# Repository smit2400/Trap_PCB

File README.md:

# TRAP — Solar-Powered Pest Trap Controller

A solar battery charger and LED driver for agricultural pest traps, built around a **Renesas RL78/G12** microcontroller with **bare-metal C** firmware. Developed at Shriji Technoaspire in 2022. By day the board charges a Li-ion battery pack from a solar panel; at night it runs from the battery and drives four LED towers that attract insects and light the farm.

*Main board, rev 2.0 — 2-layer, 61 × 70 mm (rendered from the KiCad layout)*

---

## Overview

Small farms need insect control that runs unattended and off-grid. TRAP is a single board that handles the whole day/night cycle on its own:

- **Day:** detects solar input, charges the battery and stops charging when the battery is full.
- **Night:** detects that the solar voltage has dropped and powers the LED towers from the battery.
- **Protection:** cuts the load when the battery runs low and stays off until the sun returns, so the pack is never deep-discharged.

I designed the schematic and PCB in KiCad, wrote the firmware in C, and built an Arduino-based serial programmer to flash the RL78 boards.

## Key specs

| | |
|---|---|
| **MCU** | Renesas RL78/G12 (R5F102AA), 30-pin SSOP |
| **Firmware** | Bare-metal Embedded C, Renesas CS+ / CA78K0R, Code Generator drivers |
| **Power in** | Solar panel |
| **Storage** | Li-ion battery pack, low-battery cutoff at ~7.0 V |
| **Load** | 4 LED towers via JST-EH connectors |
| **Logic supply** | MC78L05 5 V regulator |
| **Main PCB** | 2 layers, 61 × 70 mm, KiCad 6 |
| **Indicators** | CHARGING and LOW BAT status LEDs |

## Hardware

```
Solar panel ──► Schottky / Zener protection ──► Charge switch ──► Li-ion pack
                                                                     │
                     RL78 MCU ◄── ADC: solar & battery dividers ◄────┤
                        │                                            │
                        ├── charge enable / indicator LEDs           ▼
                        └── pulse output ──► LED driver (boost) ──► 4 × LED towers
```

**Main board** (`hardware/main-board/`)
- No KiCad footprint was available for the RL78/G12, so the 30-pin RL78/G13 (R5F100AC) symbol and footprint were used. This is why the schematic and BOM list the G13 part.
- Solar and battery voltages are scaled through resistor dividers into two RL78 ADC channels.
- Charging path uses SS24 Schottky diodes for reverse-current blocking and Zener clamping, with SOT-23 transistors and MOSFETs (AO3400A, TP0610T, BC847) switching the charge and load paths.
- An MC78L05 provides the 5 V logic rail.
- A 4-pin header exposes the programming and debug lines for in-circuit flashing.
- Power traces were widened from a 1.0 mm maximum in rev 1.0 to up to 1.5 mm in rev 2.0, and the ground track was widened for current handling.

**LED tower board** (`hardware/led-board/`)
- A narrow 100 × 14 mm strip of SMD LEDs; four of these form the light towers.

## Firmware

Written in bare-metal C on top of the Renesas Code Generator peripheral drivers (`r_cg_*`). The application logic lives in `r_main.c` and `r_cg_timer_user.c`.

**Sampling (timer interrupt).** Timer TAU0 channel 0 fires periodically. Each interrupt alternates between the solar ADC channel (16) and the battery ADC channel (17), accumulating samples into a moving average: 5 samples for solar, 20 for battery. The longer battery average filters out dips caused by the pulsed LED load.

**Control (main loop state machine).**

| State | Condition | Action |
|---|---|---|
| **Night / LEDs on** | Solar low, battery OK | Pulse the LED driver; switch LEDs off after a fixed on-time to save battery |
| **Charging** | Solar high, battery in range | Enable charging, CHARGING LED on, reset the night timer |
| **Battery full** | Solar high, battery at upper threshold | Stop charging |
| **Low battery** | Solar low, battery below ~7.0 V | Cut the load and latch off until solar returns |

**Flashing.** I built a programmer from an Arduino that flashes the RL78 over its serial interface, so boards could be programmed without a dedicated Renesas emulator.

**Building.** Open `firmware/Final_code.mtpj` in Renesas CS+ (CA78K0R toolchain) and build. The `r_cg_*` files are generated by the Renesas Code Generator; user code sits between the `Start user code` / `End user code` markers.

## Testing and design iterations

The board went through two fabricated revisions, with fixes found during bench and field testing.

**Rev 1.0** (May–June 2022, `hardware/revisions/rev1.0/`): first prototype. Testing found:
- The LED pulse output was routed to the wrong MCU pin.
- A transistor was used where a Schottky barrier diode was needed.
- The A49T Zener was wired in the wrong configuration.
- One indicator LED was missing its supply.

**Rev 2.0** (July 2022, `hardware/main-board/`): final design.
- Pulse output moved from pin 14 to pin 15.
- Transistor replaced with a Schottky barrier diode; symbol and footprint corrected.
- Zener configuration and charging-circuit Zener direction corrected.
- Both indicator LEDs supplied from Vo.
- Unused RST line to the boost circuit removed.
- Track widths increased; track-to-edge clearance reduced to 0.2 mm to fit a wider ground track.

**Firmware tuning** (June 2022):
- Battery averaging increased from 5 to 20 samples to reject low pulses from the LED load.
- The controller entered low-battery mode too early at 7.0 V, so the low-battery threshold was lowered from 265 to 260 ADC counts.

## Repository structure

```
Trap_PCB/
├── hardware/
│   ├── main-board/           KiCad project, rev 2.0 (final)
│   │   ├── bom/              BOM (.csv) and interactive BOM (.html)
│   │   └── fabrication/      Gerbers + drill files (.zip)
│   ├── led-board/            KiCad project for the LED tower strip
│   │   └── fabrication/
│   └── revisions/rev1.0/     First prototype, kept for reference
├── firmware/                 RL78 C source and CS+ project
└── docs/images/              Board renders
```

Open any `.kicad_pro` file in **KiCad 6** or newer. The interactive BOM opens in a browser.

## Tools

KiCad 6 · Renesas CS+ (CA78K0R) · Renesas Code Generator · Arduino · C / Embedded C

---

## Acknowledgements

Thanks to **Dhruvil Patel**, my supervisor at Shriji Technoaspire, for mentoring me through this project and helping develop the firmware.

## License

No license is granted. This repository is shared as a portfolio of my work; all rights reserved.

---

**Smit Vaghela** — Embedded Software / Firmware Engineer · [GitHub](https://github.com/smit2400)

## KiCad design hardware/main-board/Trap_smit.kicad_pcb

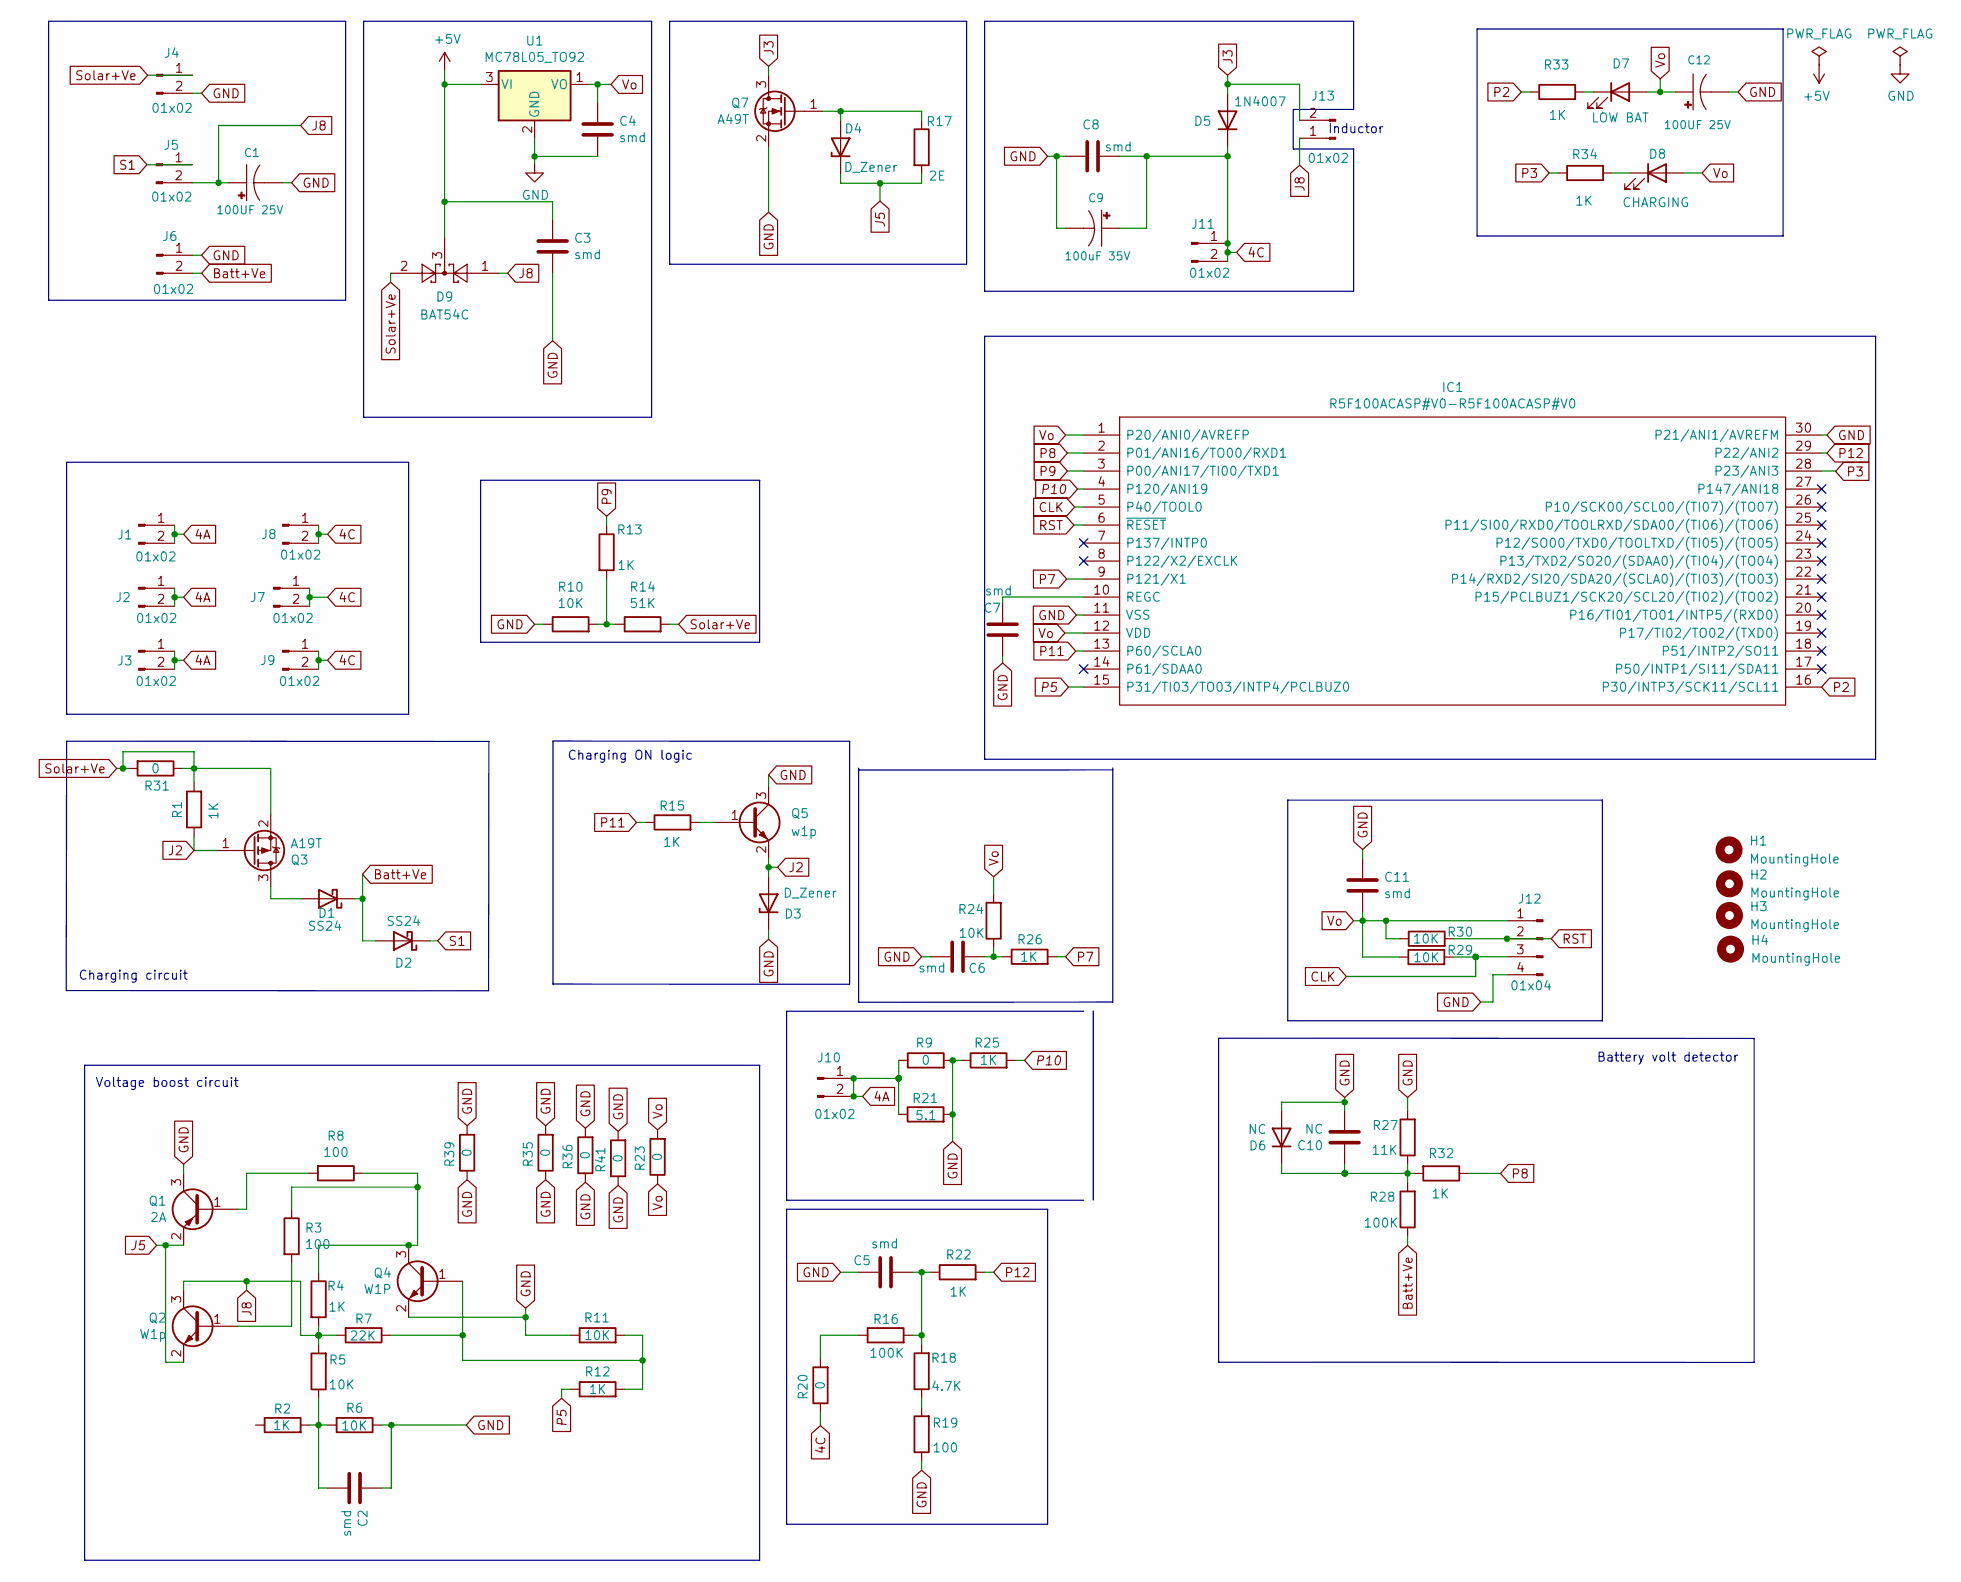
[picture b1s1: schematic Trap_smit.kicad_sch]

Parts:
C1, C12: 100UF 25V; CPOL-RADIAL-2.5MM-6.5MM
C2, C3, C4, C5, C6, C7, C8, C11: smd; 1206
C9: 100uF 35V; CAPPRD500W60D1000H1250
C10: NC; 1206
D1, D2: SS24; 1210
D3, D4: D_Zener; 1210
D5: 1N4007; 1210
D6: NC; 1210
D7: LOW BAT; LED-1206
D8: CHARGING; LED-1206
D9: BAT54C; SOT23-3
H1, H2, H3, H4: MountingHole; MountingHole_3.2mm_M3
IC1: R5F100ACASP#V0-R5F100ACASP#V0; SOP65P810X140-30N; Manufacturer_Part_Number R5F100ACASP#V0; Mouser Part Number 968-R5F100ACASP#V0
J1, J2, J3, J7, J8, J9, J10, J11: 01x02; 1X02
J4, J5, J6: 01x02; JST_EH_B2B-EH-A_1x02_P2.50mm_Vertical
J12: 01x04; 1X04
J13: 01x02; 1X02_BIG
Q1: 2A; SOT23-3
Q2: W1p; SOT23-3
Q3: A19T; SOT23-3
Q4: W1P; SOT23-3
Q5: w1p; SOT23-3
Q7: A49T; SOT23-3
R1, R2, R4, R12, R13, R15, R22, R25, R26, R32, R33, R34: 1K; 1206
R3, R8, R19: 100; 1206
R5, R6, R10, R11, R24, R29, R30: 10K; 1206
R7: 22K; 1206
R9, R20, R23, R31, R35, R36, R39, R41: 0; 1206
R14: 51K; 1206
R16, R28: 100K; 1206
R17: 2E; 1206
R18: 4.7K; 1206
R21: 5.1; 1206
R27: 11K; 1206
U1: MC78L05_TO92; SOT89R

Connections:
4A: J1.1, J1.2, J2.1, J2.2, J3.1, J3.2, J10.1, J10.2, R9.1, R21.1
4C: C8.2, C9.+, D5.1 (K), J7.1, J7.2, J8.1, J8.2, J9.1, J9.2, J11.1, J11.2, R20.1
+5V: C3.1, D9.3, U1.3 (VI)
Batt+Ve: D1.1 (K), D2.2 (A), J6.2, R28.1
CLK: IC1.5 (P40/TOOL0), J12.3, R29.2
GND: C1.2 (-), C2.1, C3.2, C4.2, C5.1, C6.2, C7.2, C8.1, C9.-, C10.2, C11.1, C12.2 (-), D3.1 (K), D6.2 (A), IC1.11 (VSS), IC1.30 (P21/ANI1/AVREFM), J4.2, J6.1, J12.4, Q1.3 (C), Q4.2 (E), Q5.3 (C), Q7.2 (S), R6.1, R9.2, R10.1, R11.1, R19.1, R21.2, R25.1, R27.2, R35.1, R35.2, R36.1, R36.2, R39.1, R39.2, R41.1, R41.2, U1.2 (GND)
J2: D3.2 (A), Q3.1 (G), Q5.2 (E), R1.1
J3: D5.2 (A), J13.2, Q7.3 (D)
J5: D4.1 (K), Q1.2 (E), Q2.2 (E), R17.2
J8: C1.1 (+), D9.1, J5.2, J13.1, Q2.3 (C), R4.2, R5.2, R7.2
unnamed: C2.2, R2.2, R5.1, R6.2
unnamed: C5.2, R16.2, R18.2, R22.1
unnamed: C6.1, R24.1, R26.1
unnamed: C7.1, IC1.10 (REGC)
unnamed: C10.1, D6.1 (K)
unnamed: D1.2 (A), Q3.3 (D)
unnamed: D4.2 (A), Q7.1 (G), R17.1
unnamed: D7.1 (K), R33.2
unnamed: D8.1 (K), R34.2
unnamed: Q1.1 (B), R8.2
unnamed: Q2.1 (B), R3.2
unnamed: Q4.1 (B), R7.1, R11.2, R12.2
unnamed: Q4.3 (C), R3.1, R4.1, R8.1
unnamed: R10.2, R13.2, R14.1
unnamed: Q5.1 (B), R15.2
unnamed: R16.1, R20.2
unnamed: R18.1, R19.2
unnamed: R27.1, R28.2, R32.2
P2: IC1.16 (P30/INTP3/SCK11/SCL11), R33.1
P3: IC1.28 (P23/ANI3), R34.1
P5: IC1.15 (P31/TI03/TO03/INTP4/PCLBUZ0), R12.1
P7: IC1.9 (P121/X1), R26.2
P8: IC1.2 (P01/ANI16/TO00/RXD1), R32.1
P9: IC1.3 (P00/ANI17/TI00/TXD1), R13.1
P10: IC1.4 (P120/ANI19), R25.2
P11: IC1.13 (P60/SCLA0), R15.1
P12: IC1.29 (P22/ANI2), R22.2
RST: IC1.6 (~RESET), J12.2, R30.2
S1: D2.1 (K), J5.1
Solar+Ve: D9.2, J4.1, Q3.2 (S), R1.2, R14.2, R31.1, R31.2
Vo: C4.1, C11.2, C12.1 (+), D7.2 (A), D8.2 (A), IC1.1 (P20/ANI0/AVREFP), IC1.12 (VDD), J12.1, R23.1, R23.2, R24.2, R29.1, R30.1, U1.1 (VO)

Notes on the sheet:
Charging ON logic
Inductor
Battery volt detector
Charging circuit
Voltage boost circuit

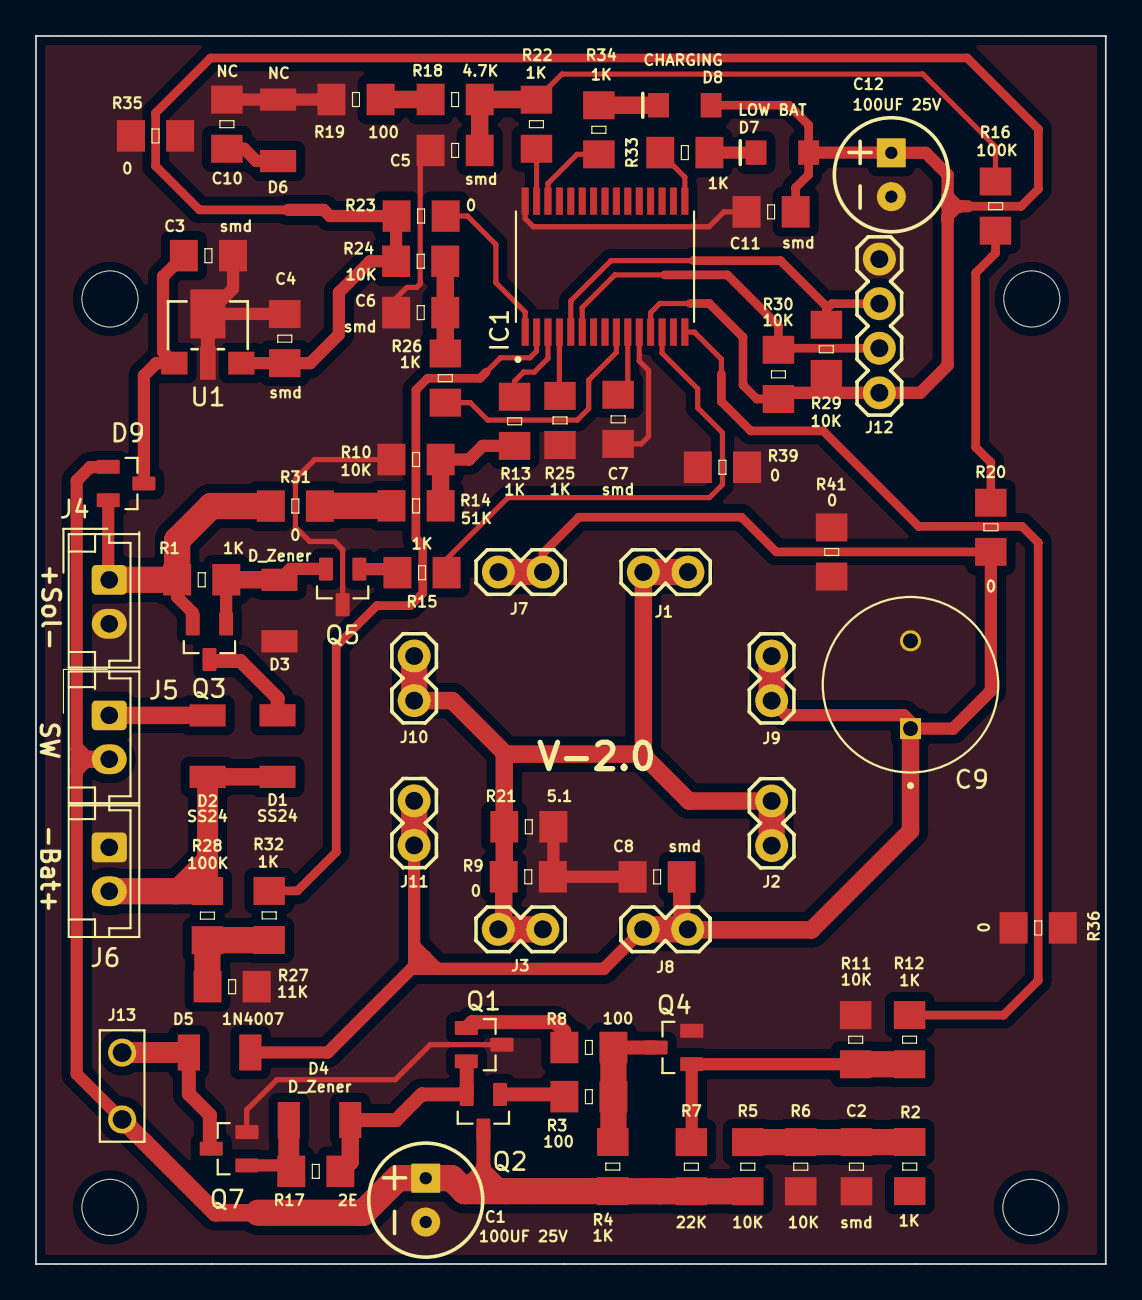
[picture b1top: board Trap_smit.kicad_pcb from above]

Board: 2 copper layers, 61.0 x 70.0 mm, 84 parts (0 on the bottom side), 41 nets.

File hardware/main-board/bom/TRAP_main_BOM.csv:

"Id";"Designator";"Package";"Quantity";"Designation";"Supplier and ref";
1;"R16,R23,R28";"1206";3;"100K";;;
2;"C12,C1";"CPOL-RADIAL-2.5MM-6.5MM";2;"100UF 25V";;;
3;"C2,C8,C4,C7,C11,C3,C5,C6";"1206";8;"smd";;;
4;"C10";"1206";1;"NC";;;
5;"J4,J6,J5";"JST_EH_B2B-EH-A_1x02_P2.50mm_Vertical";3;"01x02";;;
6;"J1,J8,J3,J7,J10,J11,J2,J9";"1X02";8;"01x02";;;
7;"R27";"1206";1;"11K";;;
8;"D1,D2";"1210";2;"D_Schottky";;;
9;"Q1";"SOT23-3";1;"2A PNP tran";;;
10;"R29,R10,R5,R30,R6,R24,R11";"1206";7;"10K";;;
11;"R4,R25,R33,R22,R26,R32,R15,R12,R2,R1,R13,R34";"1206";12;"1K";;;
12;"D3,D4";"1210";2;"D_Zener";;;
13;"IC1";"SOP65P810X140-30N";1;"R5F100ACASP#V0-R5F100ACASP#V0";;;
14;"R31,R9,R39,R41";"1206";4;"0";;;
15;"R37,R38,R20,R35,R40,R36";"1206";6;"JMP";;;
16;"R14";"1206";1;"51K";;;
17;"Q5";"SOT23-3";1;"5C2";;;
18;"R17";"1206";1;"2E";;;
19;"Q7";"SOT23-3";1;"A49T";;;
20;"R19,R8,R3";"1206";3;"100";;;
21;"D8,D7";"LED-1206";2;"LED";;;
22;"J12";"1X04";1;"01x04";;;
23;"C9";"CAPPRD500W60D1000H1250";1;"100uF 35V";;;
24;"Q2";"SOT23-3";1;"W1p";;;
25;"Q4";"SOT23-3";1;"W1P";;;
26;"U1";"SOT89R";1;"MC78L05_TO92";;;
27;"Q6";"SOT23-3";1;"W1P ";;;
28;"R18";"1206";1;"4.7K";;;
29;"R21";"1206";1;"5.1";;;
30;"D5";"1210";1;"1N4007";;;
31;"R7";"1206";1;"22K";;;
32;"D6";"1210";1;"NC";;;
33;"Q3";"SOT23-3";1;"A19T";;;
34;"J13";"1X02_BIG";1;"01x02";;;

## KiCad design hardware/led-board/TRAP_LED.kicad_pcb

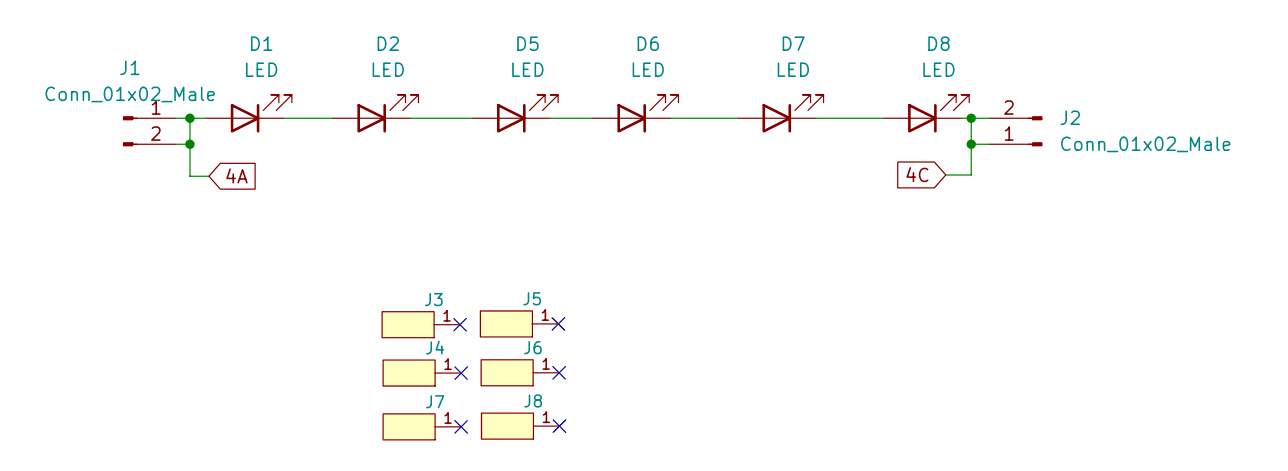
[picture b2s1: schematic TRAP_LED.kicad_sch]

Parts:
D1, D2, D5, D6, D7, D8: LED; LED_PLCC-2
J1, J2: Conn_01x02_Male; 1X02
J3, J5, J7, J8: CONN_01; Test_pad
J4, J6: CONN_01; TestPad_Trap_LED

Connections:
4A: D1.2 (A), J1.1, J1.2
4C: D8.1 (K), J2.1, J2.2
unnamed: D1.1 (K), D2.2 (A)
unnamed: D2.1 (K), D5.2 (A)
unnamed: D5.1 (K), D6.2 (A)
unnamed: D6.1 (K), D7.2 (A)
unnamed: D7.1 (K), D8.2 (A)

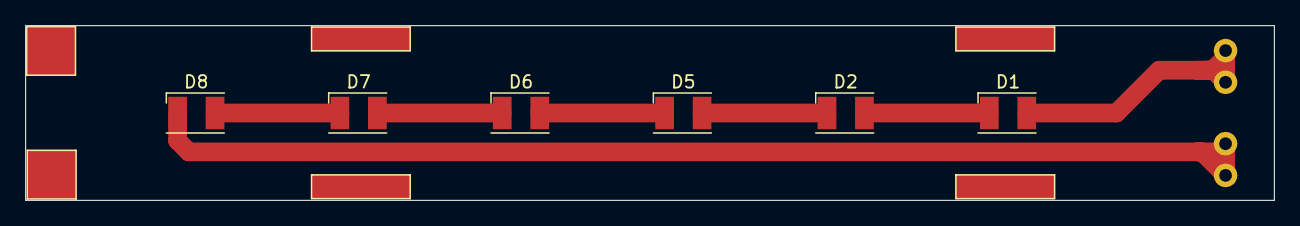
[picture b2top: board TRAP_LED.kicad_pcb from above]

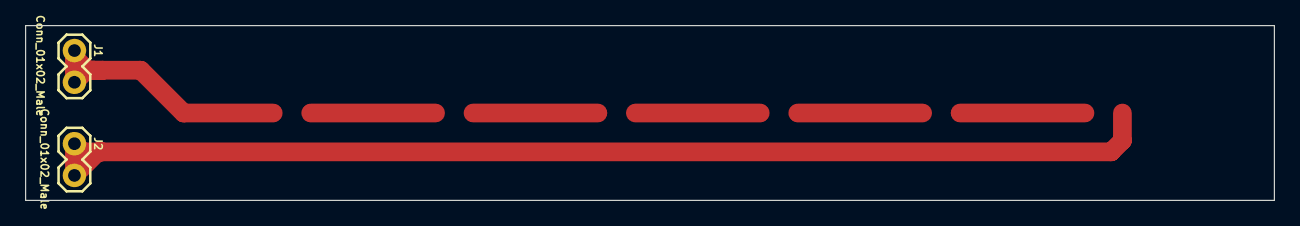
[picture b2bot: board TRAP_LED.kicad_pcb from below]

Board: 2 copper layers, 100.0 x 14.0 mm, 14 parts (2 on the bottom side), 7 nets.
